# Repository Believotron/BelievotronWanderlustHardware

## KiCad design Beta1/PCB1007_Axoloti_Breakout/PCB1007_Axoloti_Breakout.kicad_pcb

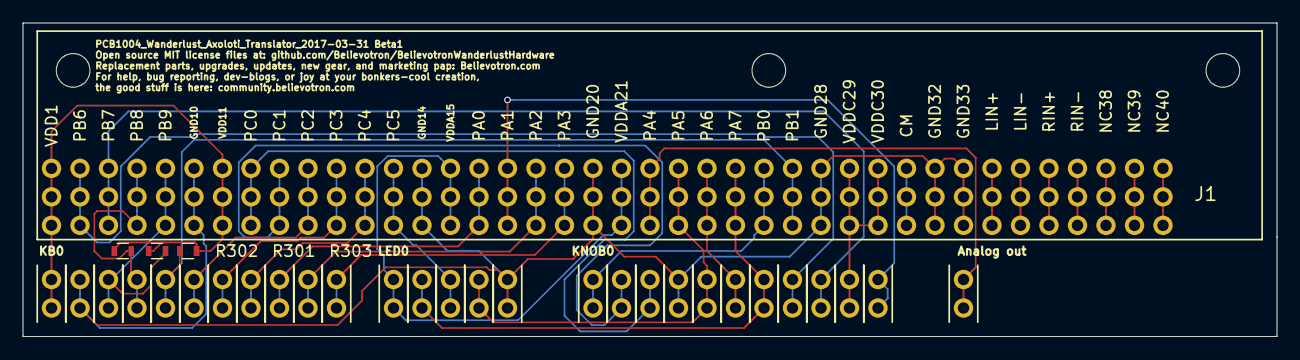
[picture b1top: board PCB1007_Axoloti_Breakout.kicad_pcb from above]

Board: 2 copper layers, 111.8 x 27.9 mm, 32 parts (0 on the bottom side), 24 nets.

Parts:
J1: Axoloti_40Pin; Axoloti-40x3
KB_+3.3V0: CONN_01X01; TH_0.1_1x2_Jumper
KB_A0, KB_A1, KB_A2, KB_A3, KB_A4, KB_A5: CONN_01X01; TH_0.1_1x2_Jumper
KB_GND0: CONN_01X01; TH_0.1_1x2_Jumper
KB_IRQ0: CONN_01X01; TH_0.1_1x2_Jumper
KB_SCL0: CONN_01X01; TH_0.1_1x2_Jumper
KB_SDA0: CONN_01X01; TH_0.1_1x2_Jumper
KNOB_+3.3V0: CONN_01X01; TH_0.1_1x2_Jumper
KNOB_ANALOG_OUT0: CONN_01X01; TH_0.1_1x2_Jumper
KNOB_GND0: CONN_01X01; TH_0.1_1x2_Jumper
KNOB_JOY_SW0: CONN_01X01; TH_0.1_1x2_Jumper
KNOB_JOY_X0: CONN_01X01; TH_0.1_1x2_Jumper
KNOB_JOY_Y0: CONN_01X01; TH_0.1_1x2_Jumper
KNOB_SPI_CLK0: CONN_01X01; TH_0.1_1x2_Jumper
KNOB_SPI_CS_0_7, KNOB_SPI_CS_8_15: CONN_01X01; TH_0.1_1x2_Jumper
KNOB_SPI_MISO0: CONN_01X01; TH_0.1_1x2_Jumper
KNOB_SPI_MOSI0: CONN_01X01; TH_0.1_1x2_Jumper
KNOB_VOL0: CONN_01X01; TH_0.1_1x2_Jumper
LED_+3.3V0: CONN_01X01; TH_0.1_1x2_Jumper
LED_GND0: CONN_01X01; TH_0.1_1x2_Jumper
LED_SPI_CLK0: CONN_01X01; TH_0.1_1x2_Jumper
LED_SPI_CS0: CONN_01X01; TH_0.1_1x2_Jumper
LED_SPI_MOSI_0: CONN_01X01; TH_0.1_1x2_Jumper
R301, R302, R303: 10K; R_0603

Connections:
/ANALOG_OUT: J1.22, KNOB_ANALOG_OUT0.1
/I2C_SCL: J1.4, KB_SCL0.1, R302.2
/I2C_SDA: J1.5, KB_SDA0.1, R301.2
/JOY_SW: J1.26, KNOB_JOY_SW0.1
/JOY_X: J1.9, KNOB_JOY_X0.1
/JOY_Y: J1.8, KNOB_JOY_Y0.1
/KB_A0: J1.10, KB_A0.1
/KB_A1: J1.11, KB_A1.1
/KB_A2: J1.12, KB_A2.1
/KB_A3: J1.16, KB_A3.1
/KB_A4: J1.18, KB_A4.1
/KB_A5: J1.19, KB_A5.1
/KB_IRQ: J1.27, KB_IRQ0.1, R303.2
/KNOB_CS_0_7: J1.3, KNOB_SPI_CS_0_7.1
/KNOB_CS_8_15: J1.2, KNOB_SPI_CS_8_15.1
/SPI_CLK: J1.23, KNOB_SPI_CLK0.1, LED_SPI_CLK0.1
/SPI_CS_LED0: J1.13, LED_SPI_CS0.1
/SPI_MISO: J1.24, KNOB_SPI_MISO0.1
/SPI_MOSI: J1.25, KNOB_SPI_MOSI0.1, LED_SPI_MOSI_0.1
/VCC_A: J1.1, J1.7, KB_+3.3V0.1, R301.1, R302.1, R303.1
/VCC_B: J1.15, J1.21, LED_+3.3V0.1
/VCC_C: J1.29, J1.30, KNOB_+3.3V0.1
/VOLUME: J1.17, KNOB_VOL0.1
GND: J1.6, J1.14, J1.20, J1.28, J1.32, J1.33, KB_GND0.1, KNOB_GND0.1, LED_GND0.1

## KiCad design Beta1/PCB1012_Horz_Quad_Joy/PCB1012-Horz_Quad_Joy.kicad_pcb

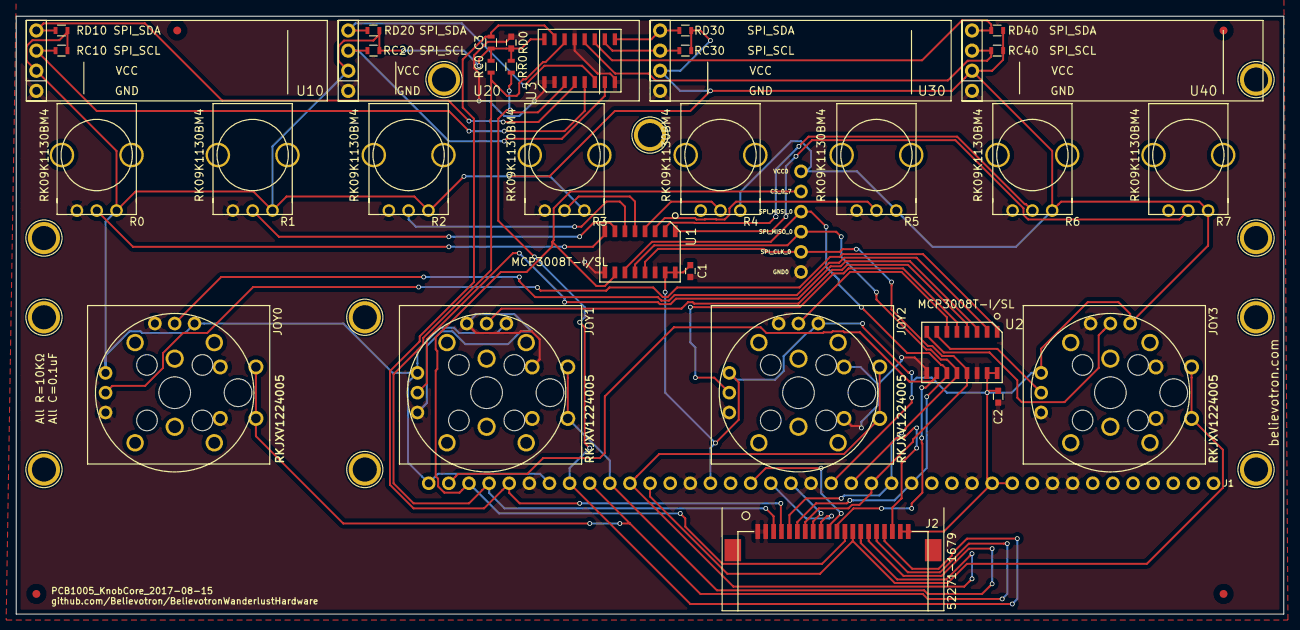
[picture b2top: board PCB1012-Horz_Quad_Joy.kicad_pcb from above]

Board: 2 copper layers, 160.0 x 75.5 mm, 41 parts (0 on the bottom side), 42 nets.

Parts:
C1, C2, C3: 0.1u; C_0603
CS_0_7: CONN_01X01; single_0.1
GND0: CONN_01X01; single_0.1
J1: Axoloti_40Pin; Axoloti-40x1_slim
J2: FPC_20POS; FFC_1MM_20POS_MOLEX_52271-2079
JOY0, JOY1, JOY2, JOY3: XYJOY_Alps; JOY_ALPS_RKJXV1224005
R0, R1, R2, R3, R4, R5, R6, R7: POT; POT_ALPS_RK09K1130BM4
RC0, RC10, RC20, RC30, RC40: 10K; R_0603
RD0, RD10, RD20, RD30, RD40: 10K; R_0603
RR0: 10K; R_0603
SPI_CLK_0: CONN_01X01; single_0.1
SPI_MISO_0: CONN_01X01; single_0.1
SPI_MOSI_0: CONN_01X01; single_0.1
U1, U2: MCP3008T-I/SL; SOIC-16
U3: I2C_1x4MUX_TCA9546A; SOIC-16_1.27x5.4
U10, U20, U30, U40: OLED_128x32_I2C; OLED_128x32
VCC0: CONN_01X01; single_0.1

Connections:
+3V3: C1.1, C2.1, C3.1, J1.1, J1.7, J1.15, J1.21, J1.29, J1.30, J2.19, J2.20, JOY0.J0-1, JOY0.J1-1, JOY1.J0-1, JOY1.J1-1, JOY2.J0-1, JOY2.J1-1, JOY3.J0-1, JOY3.J1-1, R0.1, R1.1, R2.1, R3.1, R4.1, R5.1, R6.1, R7.1, RC0.1, RC10.1, RC20.1, RC30.1, RC40.1, RD0.1, RD10.1, RD20.1, RD30.1, RD40.1, RR0.1, U1.15, U1.16, U2.15, U2.16, U3.16, U10.2, U20.2, U30.2, U40.2, VCC0.1
/!OLED_RESET: J1.8, J2.17, RR0.2, U3.3
/ANALOG_OUT: J1.22, J2.18
/CS_0_7: CS_0_7.1, J1.3, J2.12, U1.10
/CS_8_15: J1.2, J2.11, U2.10
/I2C_SCL: J1.4, J2.3, RC0.2, U3.14
/I2C_SCL0: RC10.2, U3.5, U10.3
/I2C_SCL1: RC20.2, U3.7, U20.3
/I2C_SCL2: RC30.2, U3.10, U30.3
/I2C_SCL3: RC40.2, U3.12, U40.3
/I2C_SDA: J1.5, J2.4, RD0.2, U3.15
/I2C_SDA0: RD10.2, U3.4, U10.4
/I2C_SDA1: RD20.2, U3.6, U20.4
/I2C_SDA2: RD30.2, U3.9, U30.4
/I2C_SDA3: RD40.2, U3.11, U40.4
/JOY_0_0: JOY0.J0-2, U2.1
/JOY_0_1: JOY0.J1-2, U2.2
/JOY_0_SW: J1.9, J2.16, JOY0.SW1
/JOY_1_0: JOY1.J0-2, U2.3
/JOY_1_1: JOY1.J1-2, U2.4
/JOY_1_SW: J1.10, J2.15, JOY1.SW1
/JOY_2_0: JOY2.J0-2, U2.5
/JOY_2_1: JOY2.J1-2, U2.6
/JOY_2_SW: J1.11, J2.14, JOY2.SW1
/JOY_3_0: JOY3.J0-2, U2.7
/JOY_3_1: JOY3.J1-2, U2.8
/JOY_3_SW: J1.12, J2.13, JOY3.SW1
/P0: R0.2, U1.8
/P1: R1.2, U1.7
/P2: R2.2, U1.6
/P3: R3.2, U1.5
/P4: R4.2, U1.4
/P5: R5.2, U1.3
/P6: R6.2, U1.2
/P7: R7.2, U1.1
/RX: J1.19, J2.8
/SPI_CLK: J1.23, J2.7, SPI_CLK_0.1, U1.13, U2.13
/SPI_MISO: J1.24, J2.5, SPI_MISO_0.1, U1.12, U2.12
/SPI_MOSI: J1.25, J2.6, SPI_MOSI_0.1, U1.11, U2.11
/TX: J1.18, J2.9
/VOLUME: J1.17, J2.10
GND: C1.2, C2.2, C3.2, GND0.1, J1.6, J1.14, J1.20, J1.28, J1.32, J1.33, J2.1, J2.2, JOY0.J0-3, JOY0.J1-3, JOY0.SW0, JOY1.J0-3, JOY1.J1-3, JOY1.SW0, JOY2.J0-3, JOY2.J1-3, JOY2.SW0, JOY3.J0-3, JOY3.J1-3, JOY3.SW0, R0.3, R1.3, R2.3, R3.3, R4.3, R5.3, R6.3, R7.3, U1.9, U1.14, U2.9, U2.14, U3.1, U3.2, U3.8, U3.13, U10.1, U20.1, U30.1, U40.1

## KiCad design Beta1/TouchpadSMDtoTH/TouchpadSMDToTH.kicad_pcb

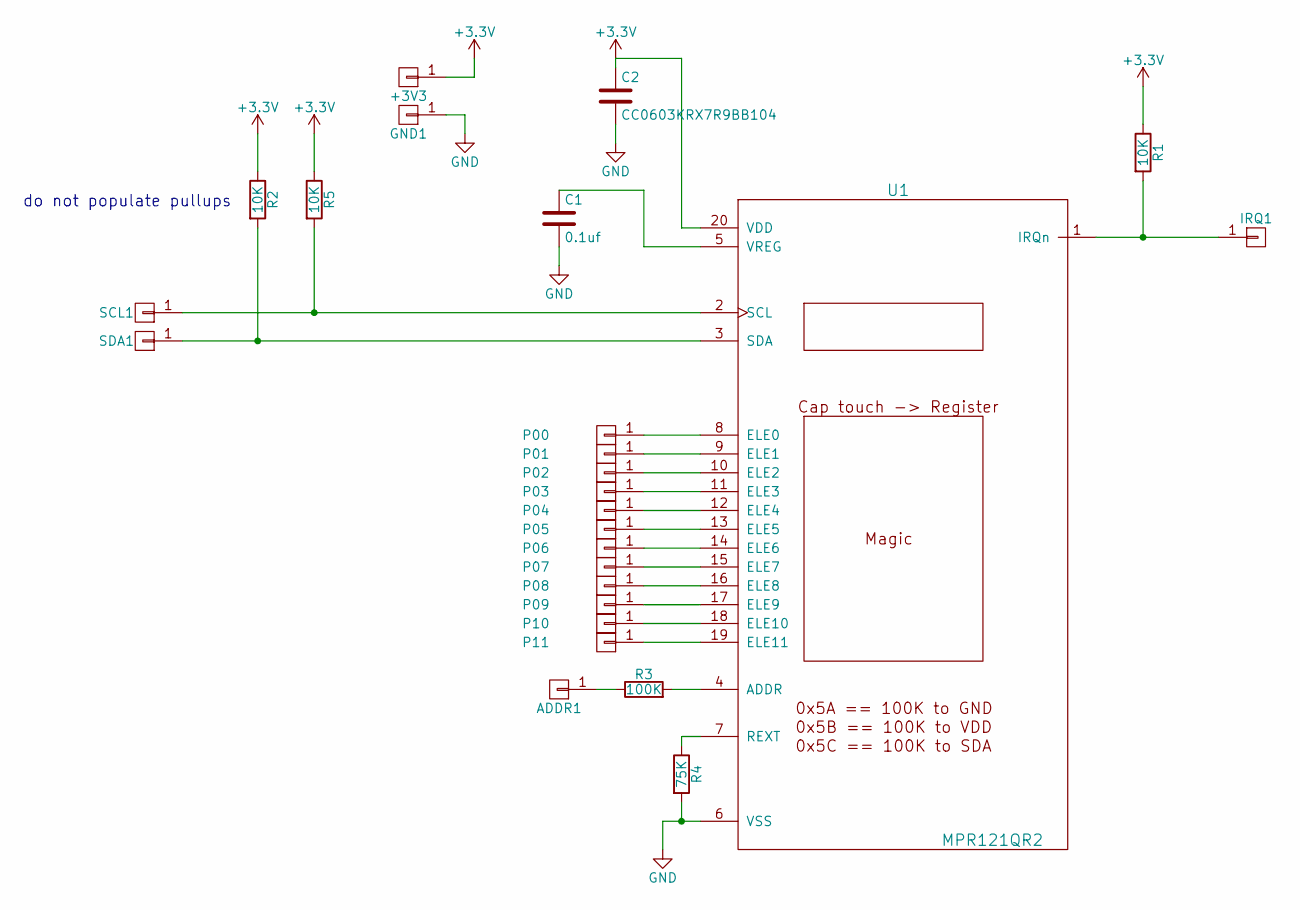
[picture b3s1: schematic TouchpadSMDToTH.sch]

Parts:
+3V3: CONN_01X01; single_0.1; MPN ON_PCB
ADDR1: CONN_01X01; single_0.1; MPN ON_PCB
C1: 0.1uf; C_0603; MPN CC0603KRX7R9BB104
C2: CC0603KRX7R9BB104; C_0603; MPN CC0603KRX7R9BB104
GND1: CONN_01X01; single_0.1; MPN ON_PCB
IRQ1: CONN_01X01; single_0.1; MPN ON_PCB
P00, P01, P02, P03, P04, P05, P06, P07, P08, P09, P10, P11: CONN_01X01; single_0.1; MPN ON_PCB
R1, R2, R5: 10K; R_0603; MPN CRCW060310K0JNEA
R3: 100K; R_0603; MPN CRCW0603100KFKEA
R4: 75K; R_0603; MPN RC0603FR-0775KL
SCL1: CONN_01X01; single_0.1; MPN ON_PCB
SDA1: CONN_01X01; single_0.1; MPN ON_PCB
U1: MPR121QR2; QFN-20-1EP_3x3mm_Pitch0.65mm

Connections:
+3V3: +3V3.1, C2.1, R1.1, R2.1, R5.1, U1.20 (VDD)
GND: C1.2, C2.2, GND1.1, R4.2, U1.6 (VSS)
unnamed: ADDR1.1, R3.1
unnamed: C1.1, U1.5 (VREG)
unnamed: IRQ1.1, R1.2, U1.1 (IRQn)
unnamed: P00.1, U1.8 (ELE0)
unnamed: P01.1, U1.9 (ELE1)
unnamed: P02.1, U1.10 (ELE2)
unnamed: P03.1, U1.11 (ELE3)
unnamed: P04.1, U1.12 (ELE4)
unnamed: P05.1, U1.13 (ELE5)
unnamed: P06.1, U1.14 (ELE6)
unnamed: P07.1, U1.15 (ELE7)
unnamed: P08.1, U1.16 (ELE8)
unnamed: P09.1, U1.17 (ELE9)
unnamed: P10.1, U1.18 (ELE10)
unnamed: P11.1, U1.19 (ELE11)
unnamed: R2.2, SDA1.1, U1.3 (SDA)
unnamed: R3.2, U1.4 (ADDR)
unnamed: R4.1, U1.7 (REXT)
unnamed: R5.2, SCL1.1, U1.2 (SCL)

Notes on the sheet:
do not populate pullups

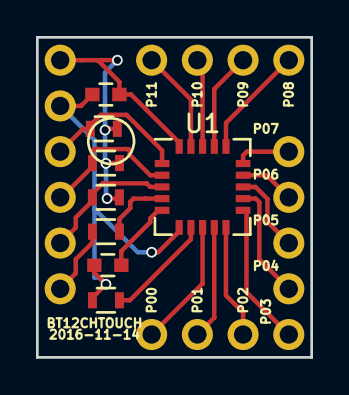
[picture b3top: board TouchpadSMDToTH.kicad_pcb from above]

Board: 2 copper layers, 15.2 x 17.8 mm, 26 parts (0 on the bottom side), 21 nets.

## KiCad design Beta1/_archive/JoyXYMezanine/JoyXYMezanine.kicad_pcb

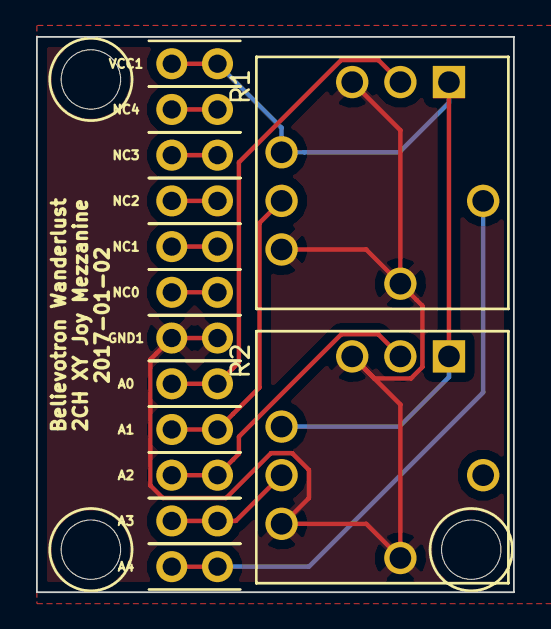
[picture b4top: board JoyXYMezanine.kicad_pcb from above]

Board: 2 copper layers, 26.5 x 30.9 mm, 14 parts (0 on the bottom side), 7 nets.

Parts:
A0, A1, A2, A3, A4: CONN_01X01; TH_0.1_1x2_Jumper
GND1: CONN_01X01; TH_0.1_1x2_Jumper
NC0, NC1, NC2, NC3, NC4: CONN_01X01; TH_0.1_1x2_Jumper
R1, R2: XYJOY; XY_JOY_254TA103B50B
VCC1: CONN_01X01; TH_0.1_1x2_Jumper

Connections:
GND: GND1.1, R1.R1.3, R1.R2.3, R1.S1.1, R2.R1.3, R2.R2.3, R2.S1.1
unnamed: A0.1, R1.R1.2
unnamed: A1.1, R1.R2.2
unnamed: A2.1, R2.R1.2
unnamed: A3.1, R2.R2.2
unnamed: A4.1, R1.S1.2
VCC: R1.R1.1, R1.R2.1, R2.R1.1, R2.R2.1, VCC1.1

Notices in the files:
Beta1/PCB1007_Axoloti_Breakout/PCB1007_Axoloti_Breakout.kicad_pcb:
Open source MIT license files at: github.com/Believotron/BelievotronWanderlustHardware
